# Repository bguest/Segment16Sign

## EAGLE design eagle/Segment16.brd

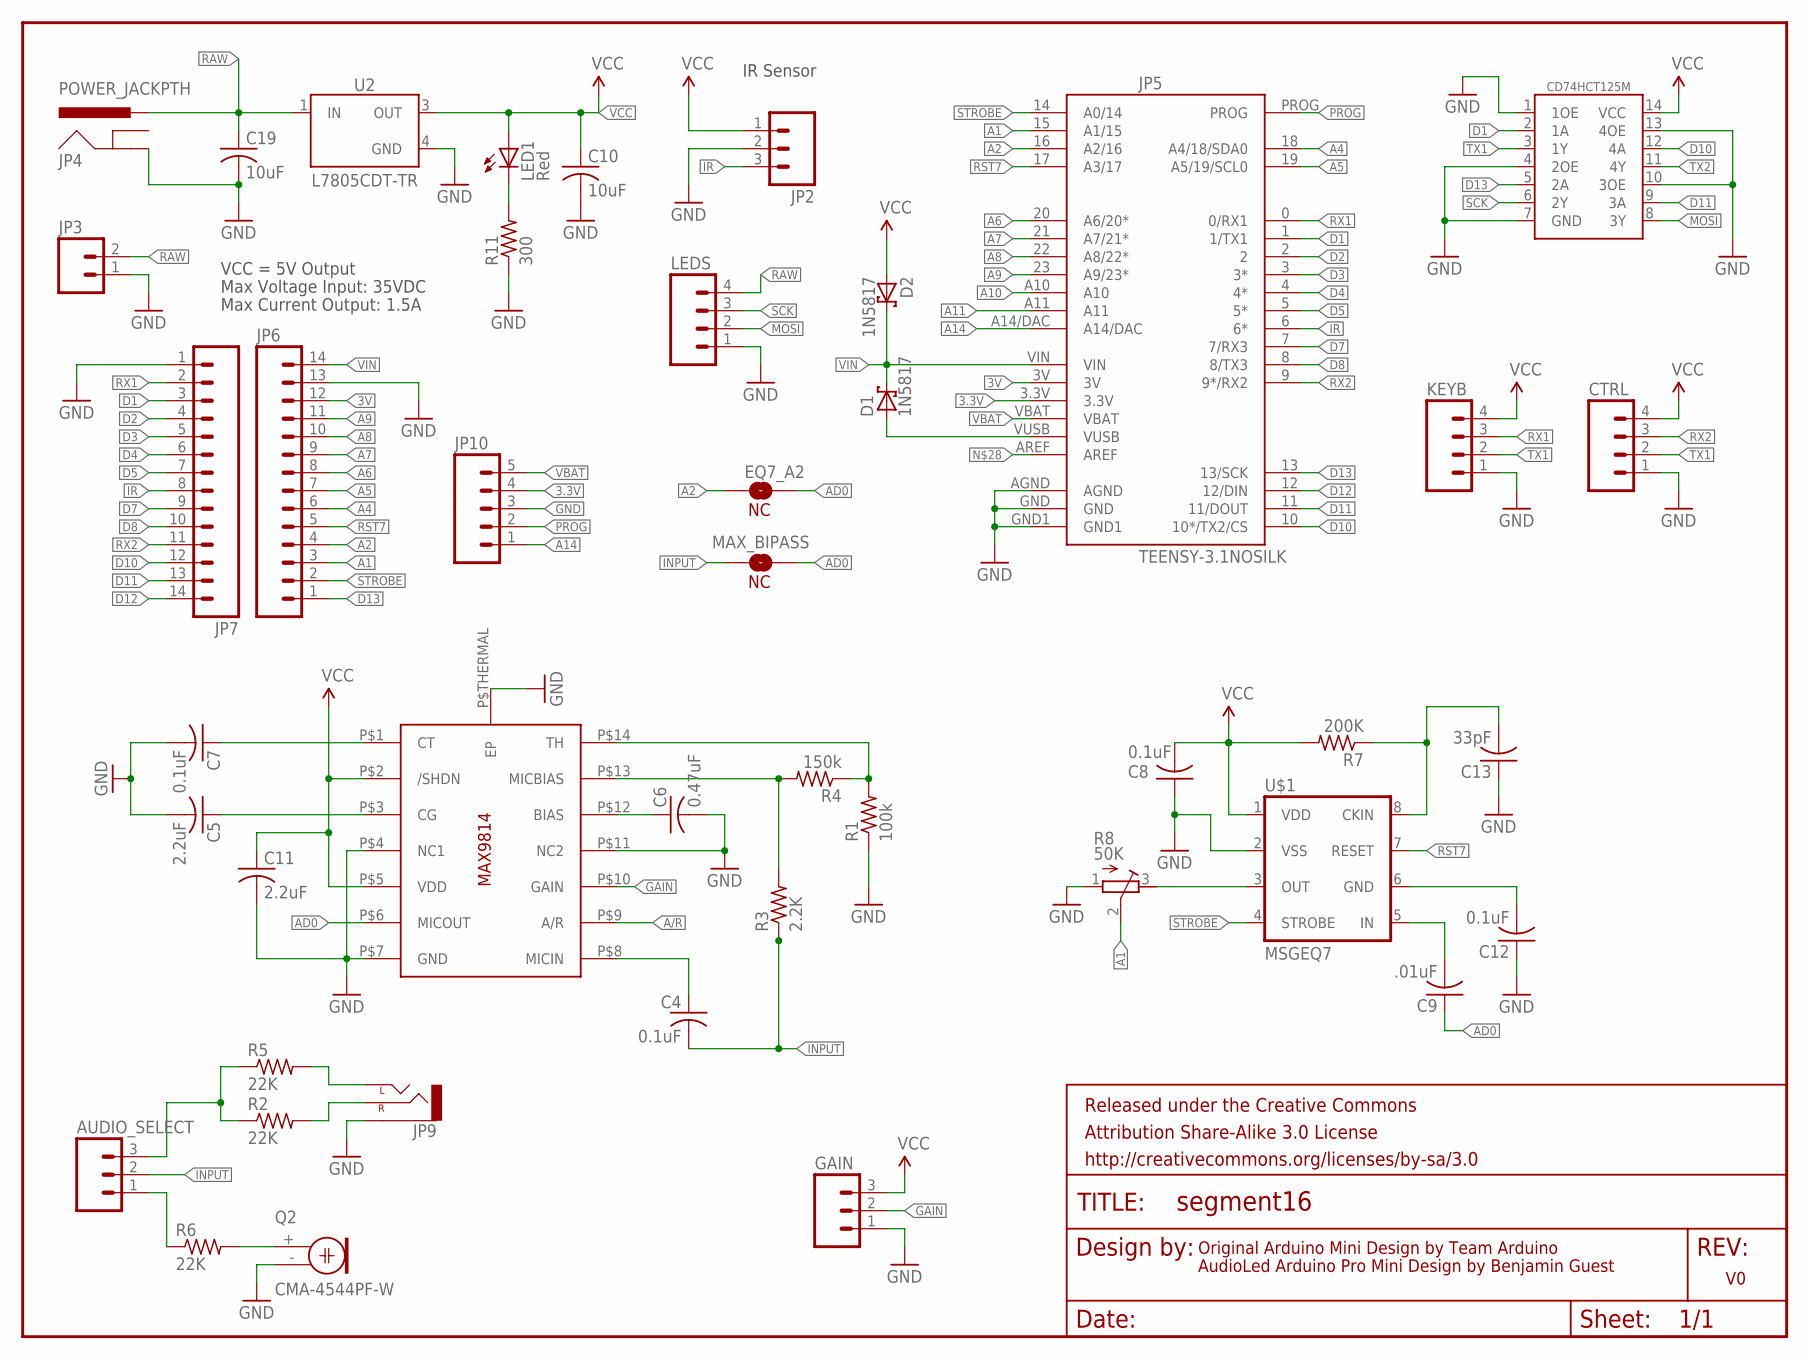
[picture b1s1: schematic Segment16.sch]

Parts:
AUDIO_SELECT: M03PTH; 1X03
C4, C7: 0.1uF; C0805K
C5, C11: 2.2uF; C0805K
C6: 0.47uF; C0805K
C8, C12: 0.1uF; C0805
C9: .01uF; C0805
C10, C19: 10uF; C0805
C13: 33pF; C0805
CD74HCT125M: CD74HCT125; SO14
CTRL: M04JST-PTH; JST-4-PTH
D1, D2: 1N5817; DO41-7.6; MPN 1N5817RLG
EQ7_A2: NC; SJ_2S
FRAME1: FRAME-LETTER; CREATIVE_COMMONS
GAIN: M03PTH; 1X03
JP2: M03JST-PTH; JST-3-PTH
JP3: M02JST-PTH-2; JST-2-PTH
JP4: POWER_JACKPTH; POWER_JACK_PTH
JP5: TEENSY-3.1NOSILK; TEENSY-3.1_NOSILK
JP6, JP7: M14; 1X14
JP9: AUDIO-JACKSMD2; AUDIO-JACK-3.5MM-SMD
JP10: M05PTH; 1X05
KEYB: M04JST-PTH; JST-4-PTH
LED1: Red; CHIPLED_0805
LEDS: M04JST-PTH; JST-4-PTH
MAX_BIPASS: NC; SJ_2S
Q2: CMA-4544PF-W; 9.7ELECTRET
R1: 100k; R0805
R2, R5, R6: 22K; M0805
R3: 2.2K; R0805
R4: 150k; R0805
R7: 200K; M0805
R8: 50K; RTRIM3296W; MPN 3296W-1-102LF
R11: 300; M0805
U2: L7805CDT-TR; DPAK
U4: MAX9814TDFN14; TDFN14_3X3MM
U$1: MSGEQ7; DIL08-ROUND

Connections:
3.3V: JP5.3.3V, JP10.4
3V: JP5.3V, JP6.12
A1: JP5.15 (A1/15), JP6.3, R8.2 (S)
A2: EQ7_A2.1, JP5.16 (A2/16), JP6.4
A4: JP5.18 (A4/18/SDA0), JP6.6
A5: JP5.19 (A5/19/SCL0), JP6.7
A6: JP5.20 (A6/20*), JP6.8
A7: JP5.21 (A7/21*), JP6.9
A8: JP5.22 (A8/22*), JP6.10
A9: JP5.23 (A9/23*), JP6.11
A10: JP5.A10
A11: JP5.A11
A14: JP5.A14/DAC, JP10.1
A/R: U4.P$9 (A/R)
AD0: C9.1, EQ7_A2.2, MAX_BIPASS.2, U4.P$6 (MICOUT)
D1: CD74HCT125M.2 (1A), JP5.1 (1/TX1), JP7.3
D2: JP5.2, JP7.4
D3: JP5.3 (3*), JP7.5
D4: JP5.4 (4*), JP7.6
D5: JP5.5 (5*), JP7.7
D7: JP5.7 (7/RX3), JP7.9
D8: JP5.8 (8/TX3), JP7.10
D10: CD74HCT125M.12 (4A), JP5.10 (10*/TX2/CS), JP7.12
D11: CD74HCT125M.9 (3A), JP5.11 (11/DOUT), JP7.13
D12: JP5.12 (12/DIN), JP7.14
D13: CD74HCT125M.5 (2A), JP5.13 (13/SCK), JP6.1
GAIN: GAIN.2, U4.P$10 (GAIN)
GND: C5.2, C6.2, C7.2, C8.1, C10.2, C11.2, C12.1, C13.1, C19.2, CD74HCT125M.1 (1OE), CD74HCT125M.4 (2OE), CD74HCT125M.7 (GND), CD74HCT125M.10 (3OE), CD74HCT125M.13 (4OE), CTRL.1, GAIN.1, JP2.2, JP3.1, JP4.GND, JP5.AGND, JP5.GND, JP5.GND1, JP6.13, JP7.1, JP9.SLEEVE, JP10.3, KEYB.1, LEDS.1, Q2.- (1), R1.1, R8.1 (A), R11.1, U2.4 (GND), U4.P$4 (NC1), U4.P$7 (GND), U4.P$11 (NC2), U4.P$THERMAL (EP), U$1.2 (VSS)
INPUT: AUDIO_SELECT.2, C4.2, MAX_BIPASS.1, R3.1
IR: JP2.3, JP5.6 (6*), JP7.8
MOSI: CD74HCT125M.8 (3Y), LEDS.2
unnamed: Q2.+ (2), R6.2
unnamed: JP9.RING (RIGHT), R2.2
unnamed: C6.1, U4.P$12 (BIAS)
unnamed: LED1.C, R11.2
unnamed: C4.1, U4.P$8 (MICIN)
unnamed: JP9.TIP (LEFT), R5.2
unnamed: D1.A, JP5.VUSB
unnamed: C7.1, U4.P$1 (CT)
unnamed: C5.1, U4.P$3 (CG)
unnamed: R1.2, R4.1, U4.P$14 (TH)
unnamed: R3.2, R4.2, U4.P$13 (MICBIAS)
unnamed: C9.2, U$1.5 (IN)
unnamed: AUDIO_SELECT.3, R2.1, R5.1
unnamed: AUDIO_SELECT.1, R6.1
unnamed: R8.3 (E), U$1.3 (OUT)
unnamed: C12.2, U$1.6 (GND)
unnamed: C13.2, R7.1, U$1.8 (CKIN)
PROG: JP5.PROG, JP10.2
RAW: C19.1, JP3.2, JP4.PWR, LEDS.4, U2.1 (IN)
RST7: JP5.17 (A3/17), JP6.5, U$1.7 (RESET)
RX1: JP5.0 (0/RX1), JP7.2, KEYB.3
RX2: CTRL.3, JP5.9 (9*/RX2), JP7.11
SCK: CD74HCT125M.6 (2Y), LEDS.3
STROBE: JP5.14 (A0/14), JP6.2, U$1.4 (STROBE)
TX1: CD74HCT125M.3 (1Y), CTRL.2, KEYB.2
TX2: CD74HCT125M.11 (4Y)
VBAT: JP5.VBAT, JP10.5
VCC: C8.2, C10.1, C11.1, CD74HCT125M.14 (VCC), CTRL.4, D2.A, GAIN.3, JP2.1, KEYB.4, LED1.A, R7.2, U2.3 (OUT), U4.P$2 (/SHDN), U4.P$5 (VDD), U$1.1 (VDD)
VIN: D1.C, D2.C, JP5.VIN, JP6.14

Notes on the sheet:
Original Arduino Mini Design by Team Arduino
AudioLed Arduino Pro Mini Design by Benjamin Guest
Max Voltage Input: 35VDC
Max Current Output: 1.5A
VCC = 5V Output
IR Sensor

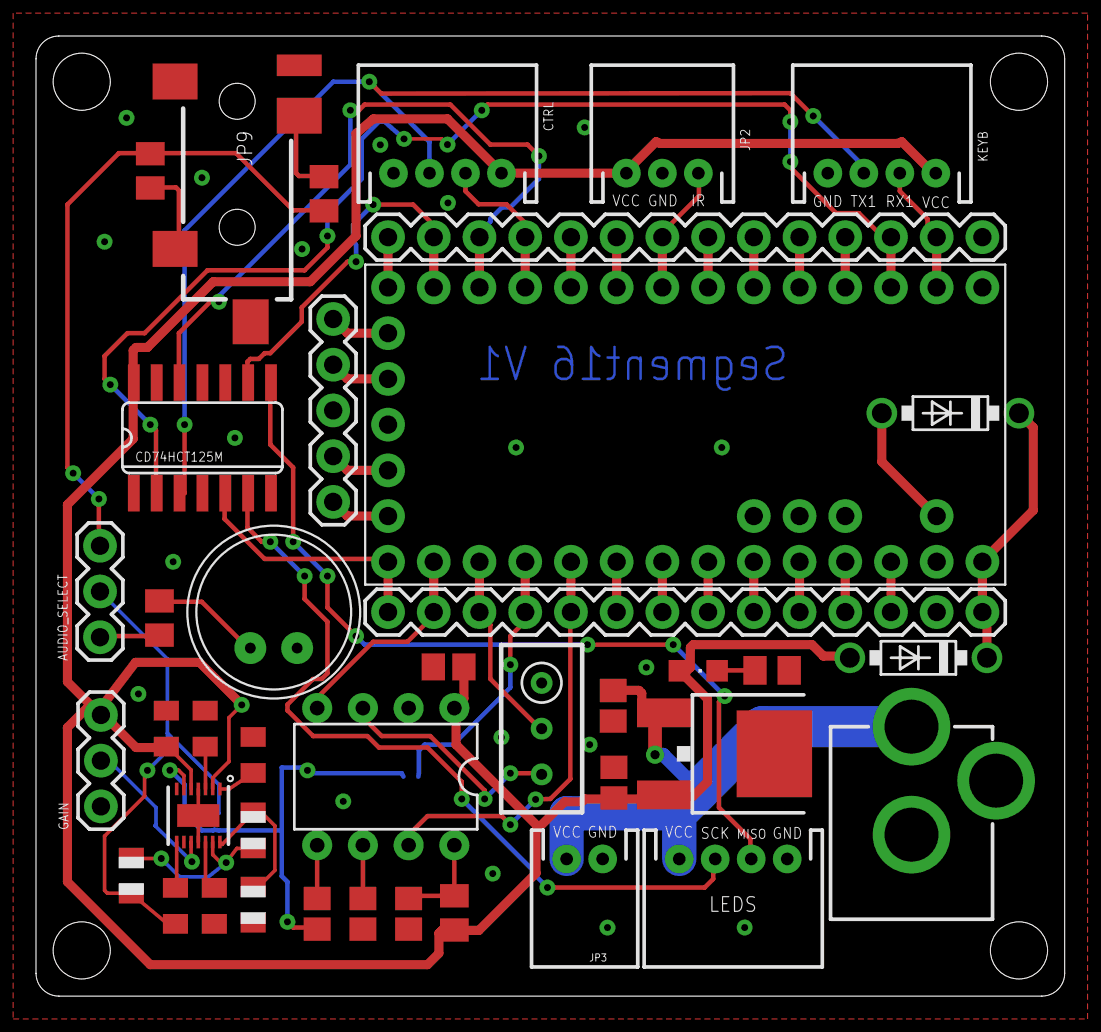
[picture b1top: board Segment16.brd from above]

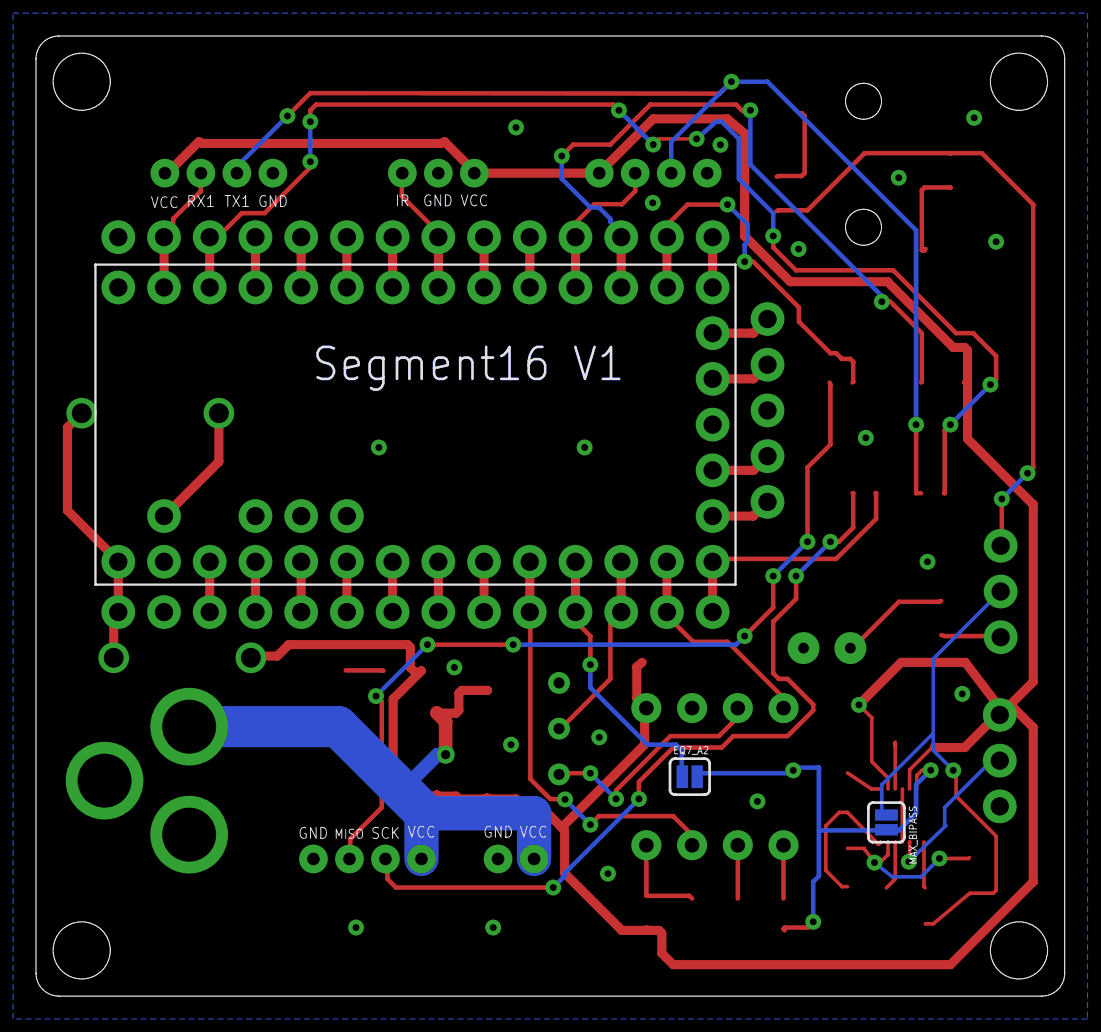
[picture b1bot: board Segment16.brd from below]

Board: 2 copper layers, 57.1 x 53.3 mm, 44 parts (2 on the bottom side), 56 nets.

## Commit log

2015-05-28 Add debug stuff
2015-05-29 Add ability to input alt characters
2015-06-28 Add Serial1
2015-06-28 Fix Serial1
2016-05-07 Updated Board to V1
2016-05-24 Add Keyboard Class
2016-05-25 Add Scrolling Effect
2016-05-26 Add ability to turn off randomize
2016-05-26 Add Pixel XY locations
2016-05-27 Add FadedY
2016-06-03 Add Sound/EffectData
2016-06-07 Add WaveXY Effect
2016-06-12 WIP: Add Single Letter Mode to scrolling
2016-06-21 Try to get MSGEQ7 to work (unsuccessfull)
2016-06-22 Fix Dimensions on board
2016-06-24 Try out Audio.h
2016-08-07 Add Seizure Mode.
2016-08-13 Add Broken Records
2018-03-01 Reindent

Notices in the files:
parts and their libraries:
SparkFun-Aesthetics: Licensing: CC v3.0 Share-Alike You are welcome to use this library for commercial purposes.
SparkFun-Aesthetics: Released under the Creative Commons Attribution Share-Alike 3.0 License
SparkFun-Aesthetics: http://creativecommons.org/licenses/by-sa/3.0
